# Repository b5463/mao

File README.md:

# MAO firmware

Firmware for **MAO**, the ODD JOBS handheld controller. Current stage: **M2** (in progress)
(ODD BUS v1 over ESP-NOW: discovery and generic capability control).

- Boards (one tree, chosen by target, see below):
  - Espressif **ESP32-C3-LCDkit** (ESP32-C3 rev v0.4, 4 MB flash, no PSRAM): the M0-M2 platform
  - **MAO_MAIN A0** (ESP32-S3-WROOM-1-N8R2: 8 MB flash, 2 MB PSRAM): the custom PCB,
    see [docs/firmware/mao-a0-firmware.md](docs/firmware/mao-a0-firmware.md)
- Framework: native ESP-IDF **v6.0.3**
- UI: LVGL 9.4 via `esp_lvgl_port`, GC9A01 240×240 round display

## Build and flash

The project uses a private ESP-IDF install at `%USERPROFILE%\esp\v6.0.3\esp-idf`
(tools in `%USERPROFILE%\.espressif`). `tools/idf.ps1` activates it for one
PowerShell process and forwards arguments to `idf.py`. Run it from
PowerShell, not Git Bash; ESP-IDF refuses to run under MSYS.

```powershell
.\tools\idf.ps1 build
.\tools\idf.ps1 -p COM13 flash monitor     # check the port first: VID:PID 303A:1001
```

Override the IDF location with `MAO_IDF_PATH` if needed.

The target selects the board (Kconfig "MAO board" follows it):

| Target | Board | Target defaults | Partition table |
|---|---|---|---|
| `esp32c3` | ESP32-C3-LCDkit | `sdkconfig.defaults.esp32c3` | `partitions.csv` (4 MB) |
| `esp32s3` | MAO_MAIN A0 | `sdkconfig.defaults.esp32s3` | `partitions_8mb.csv` (8 MB) |

`set-target` switches a build directory to another board. It deletes that
directory's generated `sdkconfig`, and each profile has its own, so run it once
per profile:

```powershell
.\tools\idf.ps1 set-target esp32s3            # dev profile -> MAO_MAIN A0
.\tools\idf.ps1 release set-target esp32s3    # release profile too
.\tools\idf.ps1 set-target esp32c3            # back to the LCDkit
```

IDF applies `sdkconfig.defaults`, then `sdkconfig.defaults.<target>`, then
the profile file. Component versions are pinned per target in
`dependencies.lock.<target>`. Without the wrapper (Linux, CI, Docker):

```sh
idf.py -B build-s3 -D SDKCONFIG=build-s3/sdkconfig \
       -D SDKCONFIG_DEFAULTS="sdkconfig.defaults;sdkconfig.dev" set-target esp32s3 build
```

Build profiles layer over `sdkconfig.defaults`:

| Profile | Command | Output | Differences |
|---|---|---|---|
| dev (default) | `.\tools\idf.ps1 build` | `build/` | dev console, perf probe, INFO logs |
| release | `.\tools\idf.ps1 release build` | `build-release/` | no console/probe, WARN logs |
| factory | `.\tools\idf.ps1 factory build` | `build-factory/` | dev + the board self-test at every boot (assembled-board validation only, never ship) |

## Layout

Data flow: drivers (input, power, IR) → event bus → `mao_app` (state) → `mao_ui` / `mao_character` / `mao_audio` / `mao_haptics` / `mao_led`.
Sensor observations (`mao_sense`) go to `mao_perception`, which posts interpreted percepts (APPROACH_NEAR, PICKED_UP,
GENTLE_PET, ...) on the event bus; the character never reads hardware and no sensor maps straight to an animation.

| Path | Purpose |
|---|---|
| `main/` | `app_main()`: bring-up sequencing only |
| `components/mao_board` | The only code that knows GPIOs, I2C addresses and board wiring. One implementation per board under `boards/` (`lcdkit/`, `main_a0/`), picked by Kconfig; pin headers are private (the A0 one is generated from `hardware/mao/design/pinmap.py`) |
| `components/mao_display` | GC9A01 + LVGL runtime, display lock, backlight, frame-performance probe |
| `components/mao_input` | Quadrature decoder (EC11 on the LCDkit, Hall ring on the A0; 30 detents/rev) and push-switch state machine, which emit MAO events |
| `components/mao_audio` | Non-blocking synthesised UI sounds: tick, notice, confirm, back |
| `components/mao_led` | WS2812 status LED: off at rest, brief pulses (A0: not fitted, calls are no-ops) |
| `components/mao_ir` | NEC IR TX/RX on the A0 (RMT); disabled on the LCDkit until its jumper is verified |
| `components/mao_haptics` | DRV2605L LRA driver and the haptic vocabulary (A0) |
| `components/mao_power` | Fuel gauge, charger/USB events, power states and sleep, deep-sleep continuity (A0) |
| `components/mao_sense` | IMU, ToF (ST VL53L4CD ULD vendored), light, touch and mic-level observations (A0) |
| `components/mao_perception` | Perception: observations + input → percepts (filters, hysteresis, fusion, confidence); platform-independent engine in `core/` |
| `components/mao_selftest` | Boot check (hardware faults, first boot of a board) and the factory / board self-test |
| `components/mao_system` | Boot banner, event bus + dispatcher, idle timer, settings (NVS `mao`), dev console |
| `components/mao_app` | Application behaviour and the authoritative app state (`mao_state.c`); reactions to percepts (`mao_app_percept.c`); power policy feed (`mao_app_power.c`) |
| `components/mao_ui` | Views: HOME, menu shell, placeholder pages, first encounter; transitions |
| `components/mao_character` | Procedural character: reaction states, idle behaviour, spring motion |
| `components/mao_radio` | Wi-Fi STA (never associated) + ESP-NOW transport |
| `components/odd_bus` | ODD BUS v1: shared, product-agnostic protocol (also used by device firmware) |
| `components/mao_devices` | ODD BUS controller: registry, discovery, liveness, confirmed value control |
| `devices/lamp_01_test` | LAMP 01: minimal ODD BUS test light (POWER, LEVEL) for a second ESP32-C3 |
| `tests/host` | Host unit tests of the perception engine and the power policy (`tests/host/run.sh`) |
| `assets/`, `tools/` | Assets (unused so far), helper scripts (incl. `factory_test.py`) |

## Development tools

With `CONFIG_MAO_DEV_CONSOLE=y` (default) the firmware accepts line commands
on the USB console. Release builds should disable it, along with
`CONFIG_MAO_PERF_PROBE`.

```powershell
python tools\mao_cmd.py COM13 help
python tools\mao_cmd.py COM13 status              # view, dial, encoder counters, heap
python tools\mao_cmd.py COM13 reset-first-boot    # clears only MAO's first-boot key
python tools\mao_cmd.py COM13 reboot
python tools\mao_cmd.py COM13 stress 20 --listen 25
python tools\mao_smoke.py COM13 --cycles 5        # scripted walk through every view and gesture
python tools\mao_cmd.py COM13 odd-selftest        # ODD BUS codec self-test on target
python tools\mao_cmd.py COM13 odd-flood 30        # 50 Hz radio load (coexistence testing)
python tools\mao_cmd.py COM13 board               # caps, revision, I2C scan, rails
python tools\mao_cmd.py COM13 sense               # A0: latest observation of every sensor
python tools\mao_cmd.py COM13 haptic heartbeat    # A0: tick double_tap heartbeat short_pulse tremor annoyed_buzz wake_pulse confirm
python tools\mao_cmd.py COM13 ir send 0x10 0x2A   # A0: one NEC frame
python tools\mao_cmd.py COM13 power               # A0: battery, charger, power state, sleep continuity
python tools\mao_cmd.py COM13 sleep 60            # A0: deep sleep, timer wake after 60 s (also: sleep light 30)
python tools\mao_cmd.py COM13 percept             # perception status; "percept inject GENTLE_PET" tries a reaction
python tools\mao_cmd.py COM13 rotate 270          # display rotation live (bring-up); "rotate save" keeps it
python tools\factory_test.py COM13                # board self-test with operator prompts (docs/hardware/mao-factory-test.md)
sh tests/host/run.sh                              # host unit tests (perception engine, power policy)
python tools\odd_m2_test.py --mao COM13 --lamp COMx   # end-to-end with LAMP 01
```

ESP-NOW runs on the fixed development channel `ODD_BUS_DEV_CHANNEL` (1) with
unencrypted peers: **development network only**.

## Partition map (4 MB, LCDkit)

| Name | Offset | Size |
|---|---|---|
| bootloader | 0x000000 | 32 KB |
| partition table | 0x008000 | 4 KB |
| nvs | 0x009000 | 24 KB |
| otadata | 0x00F000 | 8 KB |
| phy_init | 0x011000 | 4 KB |
| coredump | 0x012000 | 56 KB |
| ota_0 | 0x020000 | 1792 KB |
| ota_1 | 0x1E0000 | 1792 KB |
| assets | 0x3A0000 | 384 KB |

## Partition map (8 MB, MAO_MAIN A0)

The first 128 KB are identical to the 4 MB table.

| Name | Offset | Size |
|---|---|---|
| nvs / otadata / phy_init / coredump | 0x009000 … 0x01FFFF | as above |
| ota_0 | 0x020000 | 3072 KB |
| ota_1 | 0x320000 | 3072 KB |
| assets | 0x620000 | 1536 KB |
| (unallocated reserve) | 0x7A0000 | 384 KB |

## Recovery

A verified dump of the original factory firmware lives in `../backup/`
(SHA-256 `a15e09ff…41c10`). To restore it:

```powershell
python -m esptool --port COM13 write-flash 0x0 ..\backup\mao_flash_full_20260923.bin
```

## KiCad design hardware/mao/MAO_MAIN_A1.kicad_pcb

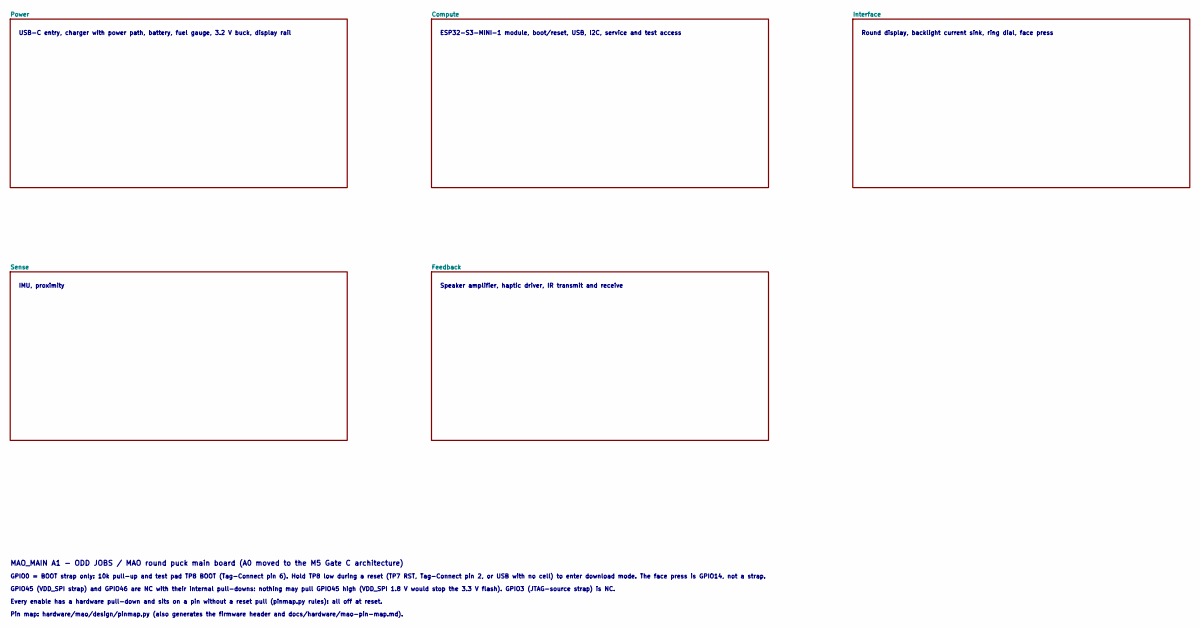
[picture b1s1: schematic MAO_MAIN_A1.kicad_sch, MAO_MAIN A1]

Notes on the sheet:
USB-C entry, charger with power path, battery, fuel gauge, 3.2 V buck, display rail
ESP32-S3-MINI-1 module, boot/reset, USB, I2C, service and test access
Round display, backlight current sink, ring dial, face press
IMU, proximity
Speaker amplifier, haptic driver, IR transmit and receive
MAO_MAIN A1 - ODD JOBS / MAO round puck main board (A0 moved to the M5 Gate C architecture)
GPIO0 = BOOT strap only: 10k pull-up and test pad TP8 BOOT (Tag-Connect pin 6). Hold TP8 low during a reset (TP7 RST, Tag-Connect pin 2, or USB with no cell) to enter download mode. The face press is GPIO14, not a strap.
GPIO45 (VDD_SPI strap) and GPIO46 are NC with their internal pull-downs: nothing may pull GPIO45 high (VDD_SPI 1.8 V would stop the 3.3 V flash). GPIO3 (JTAG-source strap) is NC.
Every enable has a hardware pull-down and sits on a pin without a reset pull (pinmap.py rules): all off at reset.
Pin map: hardware/mao/design/pinmap.py (also generates the firmware header and docs/hardware/mao-pin-map.md).

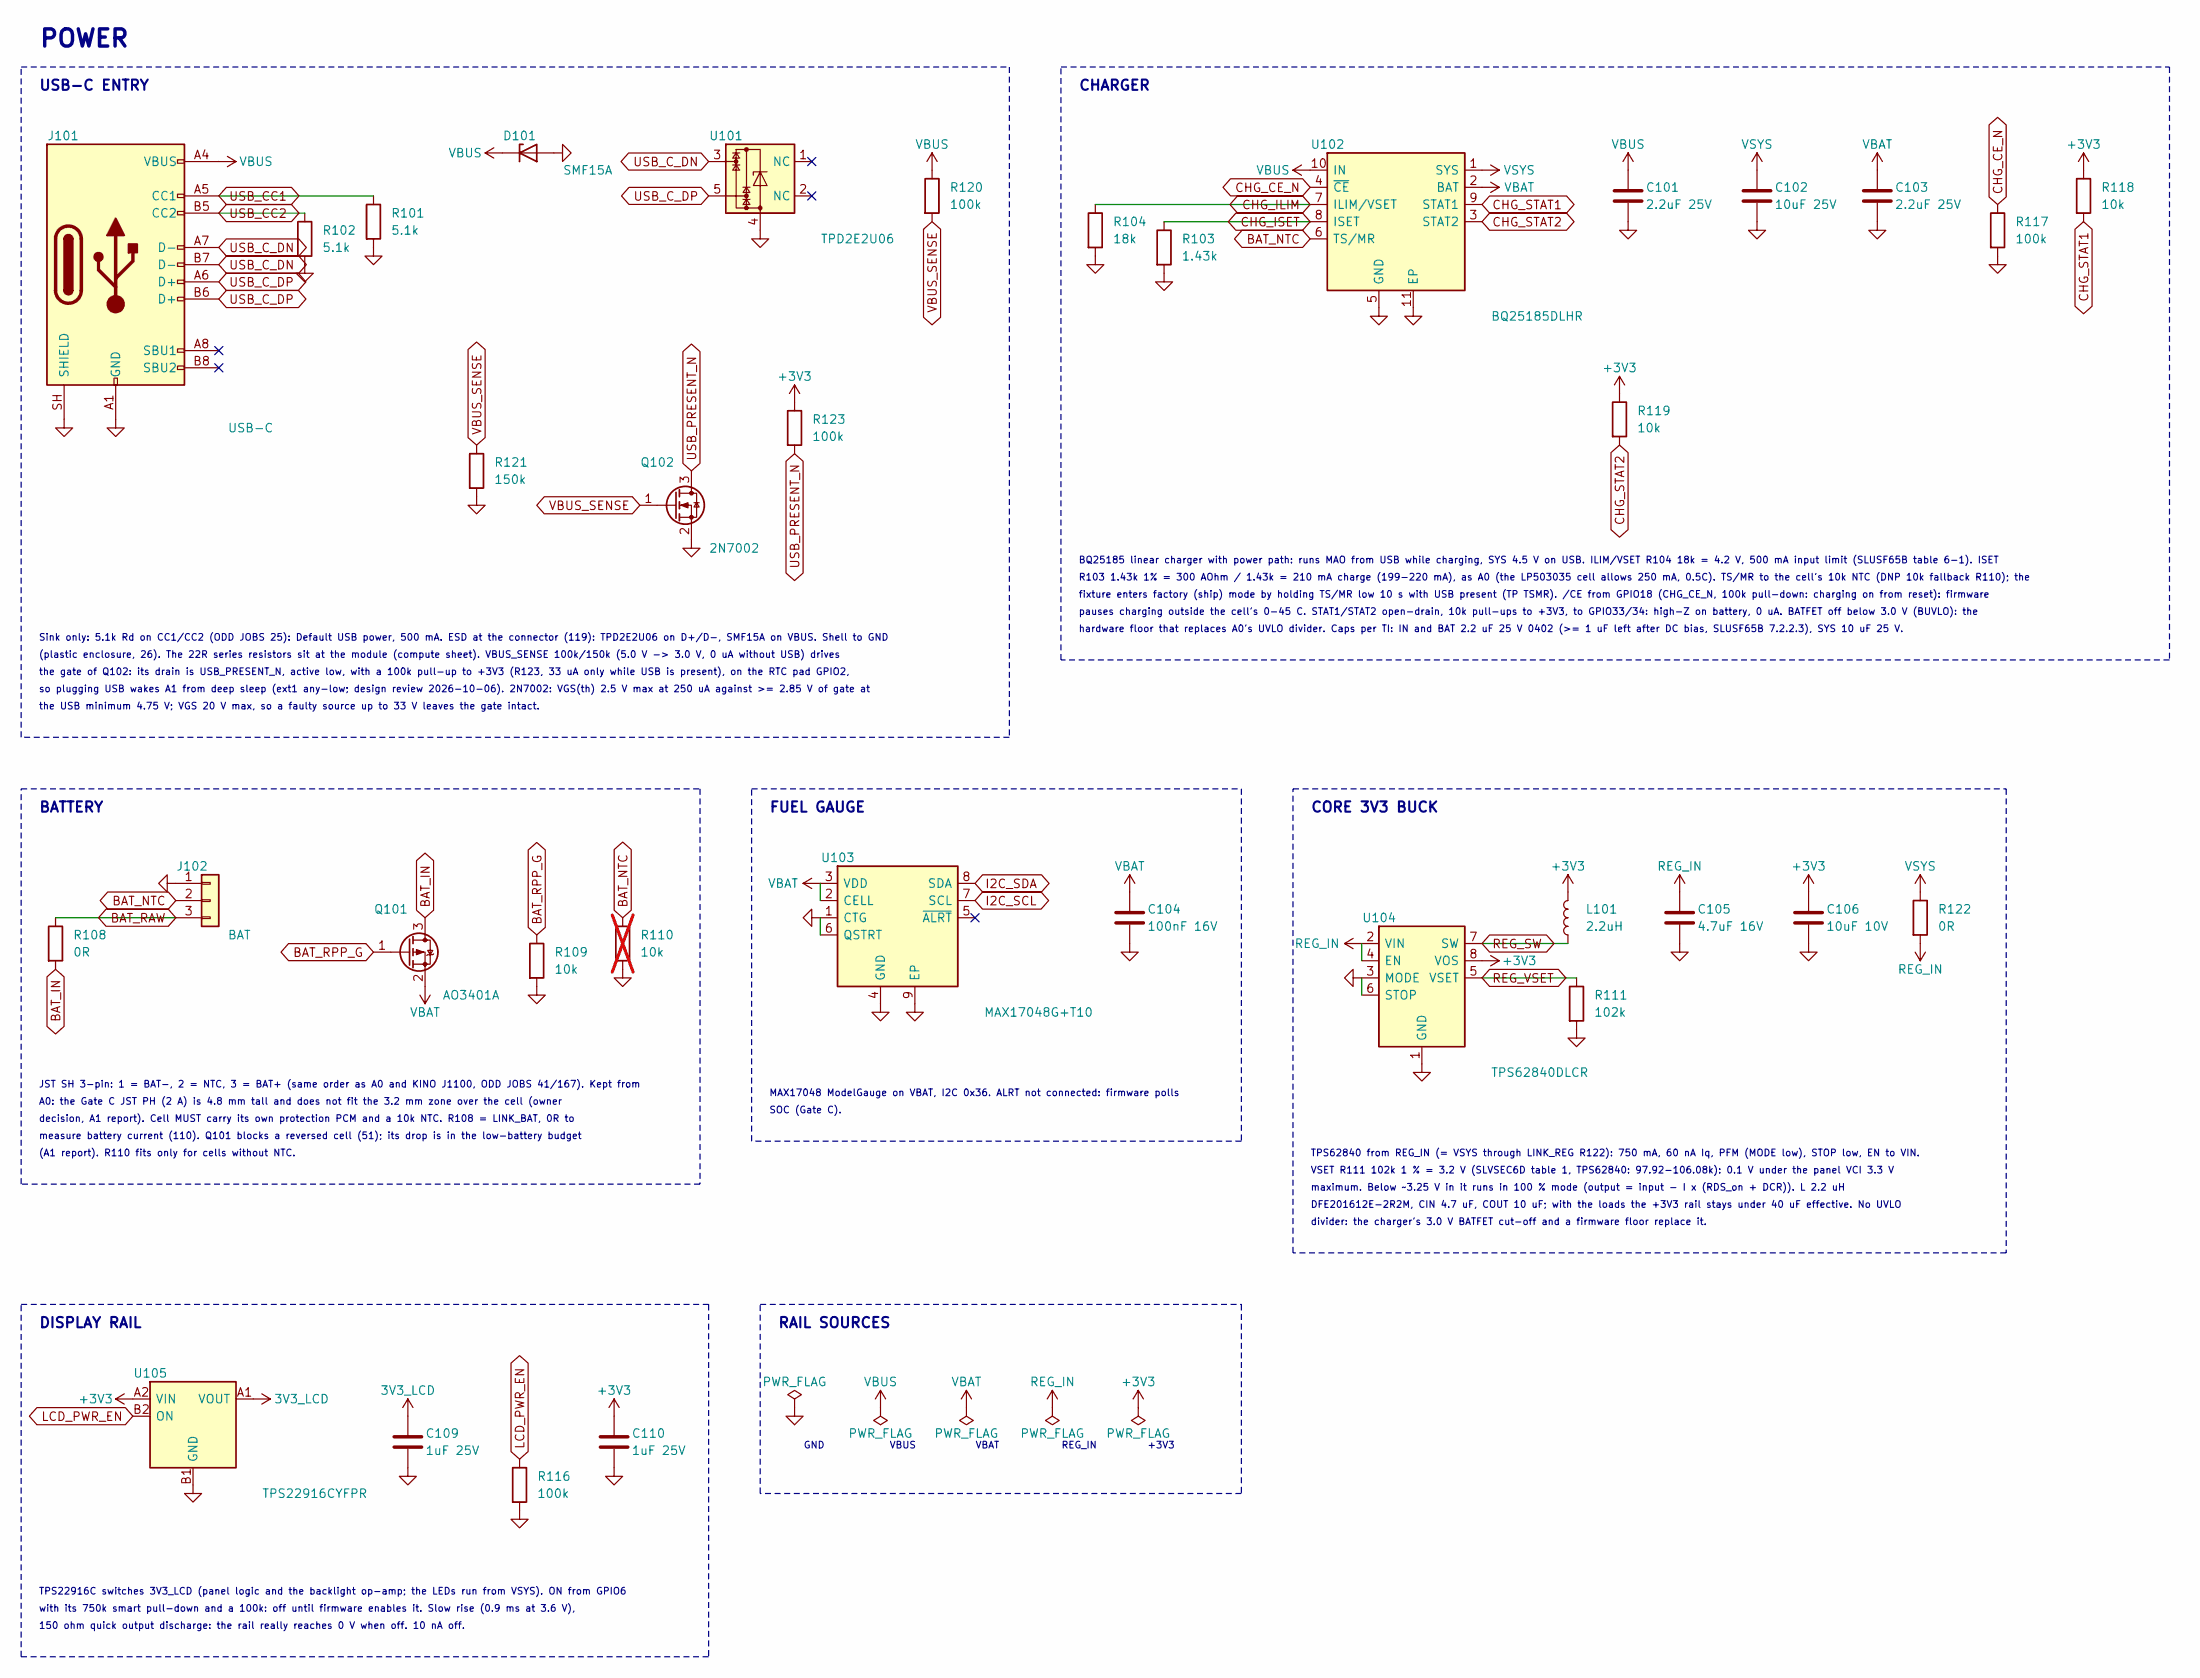
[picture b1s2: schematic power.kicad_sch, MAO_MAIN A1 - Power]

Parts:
C101, C103: 2.2uF 25V; C_0402_1005Metric; MPN CL05A225KA5NUNC; LCSC C307418
C102: 10uF 25V; C_0603_1608Metric; MPN CL10A106MA8NRNC; LCSC C96446
C104: 100nF 16V; C_0402_1005Metric; MPN CL05B104KO5NNNC; LCSC C1525
C105: 4.7uF 16V; C_0603_1608Metric; MPN CL10A475KO8NNNC; LCSC C19666
C106: 10uF 10V; C_0603_1608Metric; MPN CL10A106KP8NNNC; LCSC C19702
C109, C110: 1uF 25V; C_0402_1005Metric; MPN CL05A105KA5NQNC; LCSC C52923
D101: SMF15A; D_SMF; MPN SMF15A; LCSC C123802
J101: USB-C; USB_C_Receptacle_HRO_TYPE-C-31-M-12; MPN TYPE-C-31-M-12; LCSC C165948
J102: BAT; JST_SH_SM03B-SRSS-TB_1x03-1MP_P1.00mm_Horizontal; MPN ZX-SH1.0-3PWT (JST SM03B-SRSS-TB compat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; LCSC C7430445
L101: 2.2uH; L_Murata_DFE201610P; MPN DFE201612E-2R2M=P2; LCSC C337893
Q101: AO3401A; SOT-23; MPN AO3401A; LCSC C15127
Q102: 2N7002; SOT-23; MPN 2N7002; LCSC C8545
R101, R102: 5.1k; R_0402_1005Metric; MPN 0402WGF5101TCE; LCSC C25905
R103: 1.43k; R_0402_1005Metric; MPN RC0402FR-071K43L; LCSC C163483
R104: 18k; R_0402_1005Metric; MPN 0402WGF1802TCE; LCSC C25762
R108: 0R; R_1206_3216Metric; MPN 1206W4F0000T5E; LCSC C17888
R109, R118, R119: 10k; R_0402_1005Metric; MPN 0402WGF1002TCE; LCSC C25744
R110: 10k; R_0402_1005Metric; MPN 0402WGF1002TCE; LCSC C25744; not fitted
R111: 102k; R_0402_1005Metric; MPN FRC0402F1023TS; LCSC C2933066
R116, R117, R120, R123: 100k; R_0402_1005Metric; MPN 0402WGF1003TCE; LCSC C25741
R121: 150k; R_0402_1005Metric; MPN 0402WGF1503TCE; LCSC C25755
R122: 0R; R_0603_1608Metric; MPN 0603WAF0000T5E; LCSC C21189
U101: TPD2E2U06; SOT-553; MPN TPD2E2U06DRLR; LCSC C1972959
U102: BQ25185DLHR; Texas_DLH0010A_WSON-10-1EP_2.2x2mm_P0.4mm_EP0.9x1.5mm; MPN BQ25185DLHR; LCSC C19725033
U103: MAX17048G+T10; TDFN-8-1EP_2x2mm_P0.5mm_EP0.8x1.2mm; MPN MAX17048G+T10; LCSC C2682616
U104: TPS62840DLCR; TI_DLC0008B_VSON-HR-8_1.5x2mm_P0.5mm; MPN TPS62840DLCR; LCSC C2071859
U105: TPS22916CYFPR; Texas_PicoStar_BGA-4_0.758x0.758mm_Layout2x2_P0.4mm; MPN TPS22916CYFPR; LCSC C2680319

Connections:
3V3_LCD: C109.1, U105.A1 (VOUT); also elsewhere on the board
+3V3: C106.1, C110.1, L101.2, R118.1, R119.1, R123.1, U104.8 (VOS), U105.A2 (VIN); also elsewhere on the board
BAT_IN: Q101.3 (D), R108.2
BAT_NTC: J102.2, R110.1, U102.6 (TS/MR); also elsewhere on the board
BAT_RAW: J102.3, R108.1
BAT_RPP_G: Q101.1 (G), R109.1
CHG_CE_N: R117.1, U102.4 (~CE); also elsewhere on the board
CHG_ILIM: R104.1, U102.7 (ILIM/VSET)
CHG_ISET: R103.1, U102.8 (ISET)
CHG_STAT1: R118.2, U102.9 (STAT1); also elsewhere on the board
CHG_STAT2: R119.2, U102.3 (STAT2); also elsewhere on the board
GND: C101.2, C102.2, C103.2, C104.2, C105.2, C106.2, C109.2, C110.2, D101.2 (A), J101.A1 (GND), J101.A12 (GND), J101.B1 (GND), J101.B12 (GND), J101.SH (SHIELD), J102.1, Q102.2 (S), R101.2, R102.2, R103.2, R104.2, R109.2, R110.2, R111.2, R116.2, R117.2, R121.2, U101.4, U102.5 (GND), U102.11 (EP), U103.1 (CTG), U103.4 (GND), U103.6 (QSTRT), U103.9 (EP), U104.1 (GND), U104.3 (MODE), U104.6 (STOP), U105.B1 (GND); also elsewhere on the board
I2C_SCL: U103.7 (SCL); also elsewhere on the board
I2C_SDA: U103.8 (SDA); also elsewhere on the board
LCD_PWR_EN: R116.1, U105.B2 (ON); also elsewhere on the board
REG_IN: C105.1, R122.2, U104.2 (VIN), U104.4 (EN)
REG_SW: L101.1, U104.7 (SW)
REG_VSET: R111.1, U104.5 (VSET)
USB_CC1: J101.A5 (CC1), R101.1
USB_CC2: J101.B5 (CC2), R102.1
USB_C_DN: J101.A7 (D-), J101.B7 (D-), U101.3; also elsewhere on the board
USB_C_DP: J101.A6 (D+), J101.B6 (D+), U101.5; also elsewhere on the board
USB_PRESENT_N: Q102.3 (D), R123.2; also elsewhere on the board
VBAT: C103.1, C104.1, Q101.2 (S), U102.2 (BAT), U103.2 (CELL), U103.3 (VDD); also elsewhere on the board
VBUS: C101.1, D101.1 (K), J101.A4 (VBUS), J101.A9 (VBUS), J101.B4 (VBUS), J101.B9 (VBUS), R120.1, U102.10 (IN); also elsewhere on the board
VBUS_SENSE: Q102.1 (G), R120.2, R121.1
VSYS: C102.1, R122.1, U102.1 (SYS); also elsewhere on the board

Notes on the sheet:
POWER
USB-C ENTRY
Sink only: 5.1k Rd on CC1/CC2 (ODD JOBS 25): Default USB power, 500 mA. ESD at the connector (119): TPD2E2U06 on D+/D-, SMF15A on VBUS. Shell to GND
(plastic enclosure, 26). The 22R series resistors sit at the module (compute sheet). VBUS_SENSE 100k/150k (5.0 V -> 3.0 V, 0 uA without USB) drives
the gate of Q102: its drain is USB_PRESENT_N, active low, with a 100k pull-up to +3V3 (R123, 33 uA only while USB is present), on the RTC pad GPIO2,
so plugging USB wakes A1 from deep sleep (ext1 any-low; design review 2026-10-06). 2N7002: VGS(th) 2.5 V max at 250 uA against >= 2.85 V of gate at
the USB minimum 4.75 V; VGS 20 V max, so a faulty source up to 33 V leaves the gate intact.
CHARGER
BQ25185 linear charger with power path: runs MAO from USB while charging, SYS 4.5 V on USB. ILIM/VSET R104 18k = 4.2 V, 500 mA input limit (SLUSF65B table 6-1). ISET
R103 1.43k 1% = 300 AOhm / 1.43k = 210 mA charge (199-220 mA), as A0 (the LP503035 cell allows 250 mA, 0.5C). TS/MR to the cell's 10k NTC (DNP 10k fallback R110); the
fixture enters factory (ship) mode by holding TS/MR low 10 s with USB present (TP TSMR). /CE from GPIO18 (CHG_CE_N, 100k pull-down: charging on from reset): firmware
pauses charging outside the cell's 0-45 C. STAT1/STAT2 open-drain, 10k pull-ups to +3V3, to GPIO33/34: high-Z on battery, 0 uA. BATFET off below 3.0 V (BUVLO): the
hardware floor that replaces A0's UVLO divider. Caps per TI: IN and BAT 2.2 uF 25 V 0402 (>= 1 uF left after DC bias, SLUSF65B 7.2.2.3), SYS 10 uF 25 V.
BATTERY
JST SH 3-pin: 1 = BAT-, 2 = NTC, 3 = BAT+ (same order as A0 and KINO J1100, ODD JOBS 41/167). Kept from
A0: the Gate C JST PH (2 A) is 4.8 mm tall and does not fit the 3.2 mm zone over the cell (owner
decision, A1 report). Cell MUST carry its own protection PCM and a 10k NTC. R108 = LINK_BAT, 0R to
measure battery current (110). Q101 blocks a reversed cell (51); its drop is in the low-battery budget
(A1 report). R110 fits only for cells without NTC.
FUEL GAUGE
MAX17048 ModelGauge on VBAT, I2C 0x36. ALRT not connected: firmware polls
SOC (Gate C).
CORE 3V3 BUCK
TPS62840 from REG_IN (= VSYS through LINK_REG R122): 750 mA, 60 nA Iq, PFM (MODE low), STOP low, EN to VIN.
VSET R111 102k 1 % = 3.2 V (SLVSEC6D table 1, TPS62840: 97.92-106.08k): 0.1 V under the panel VCI 3.3 V
maximum. Below ~3.25 V in it runs in 100 % mode (output = input - I x (RDS_on + DCR)). L 2.2 uH
DFE201612E-2R2M, CIN 4.7 uF, COUT 10 uF; with the loads the +3V3 rail stays under 40 uF effective. No UVLO
divider: the charger's 3.0 V BATFET cut-off and a firmware floor replace it.
DISPLAY RAIL
TPS22916C switches 3V3_LCD (panel logic and the backlight op-amp; the LEDs run from VSYS). ON from GPIO6
with its 750k smart pull-down and a 100k: off until firmware enables it. Slow rise (0.9 ms at 3.6 V),
150 ohm quick output discharge: the rail really reaches 0 V when off. 10 nA off.
RAIL SOURCES
GND
VBUS
VBAT
REG_IN
+3V3

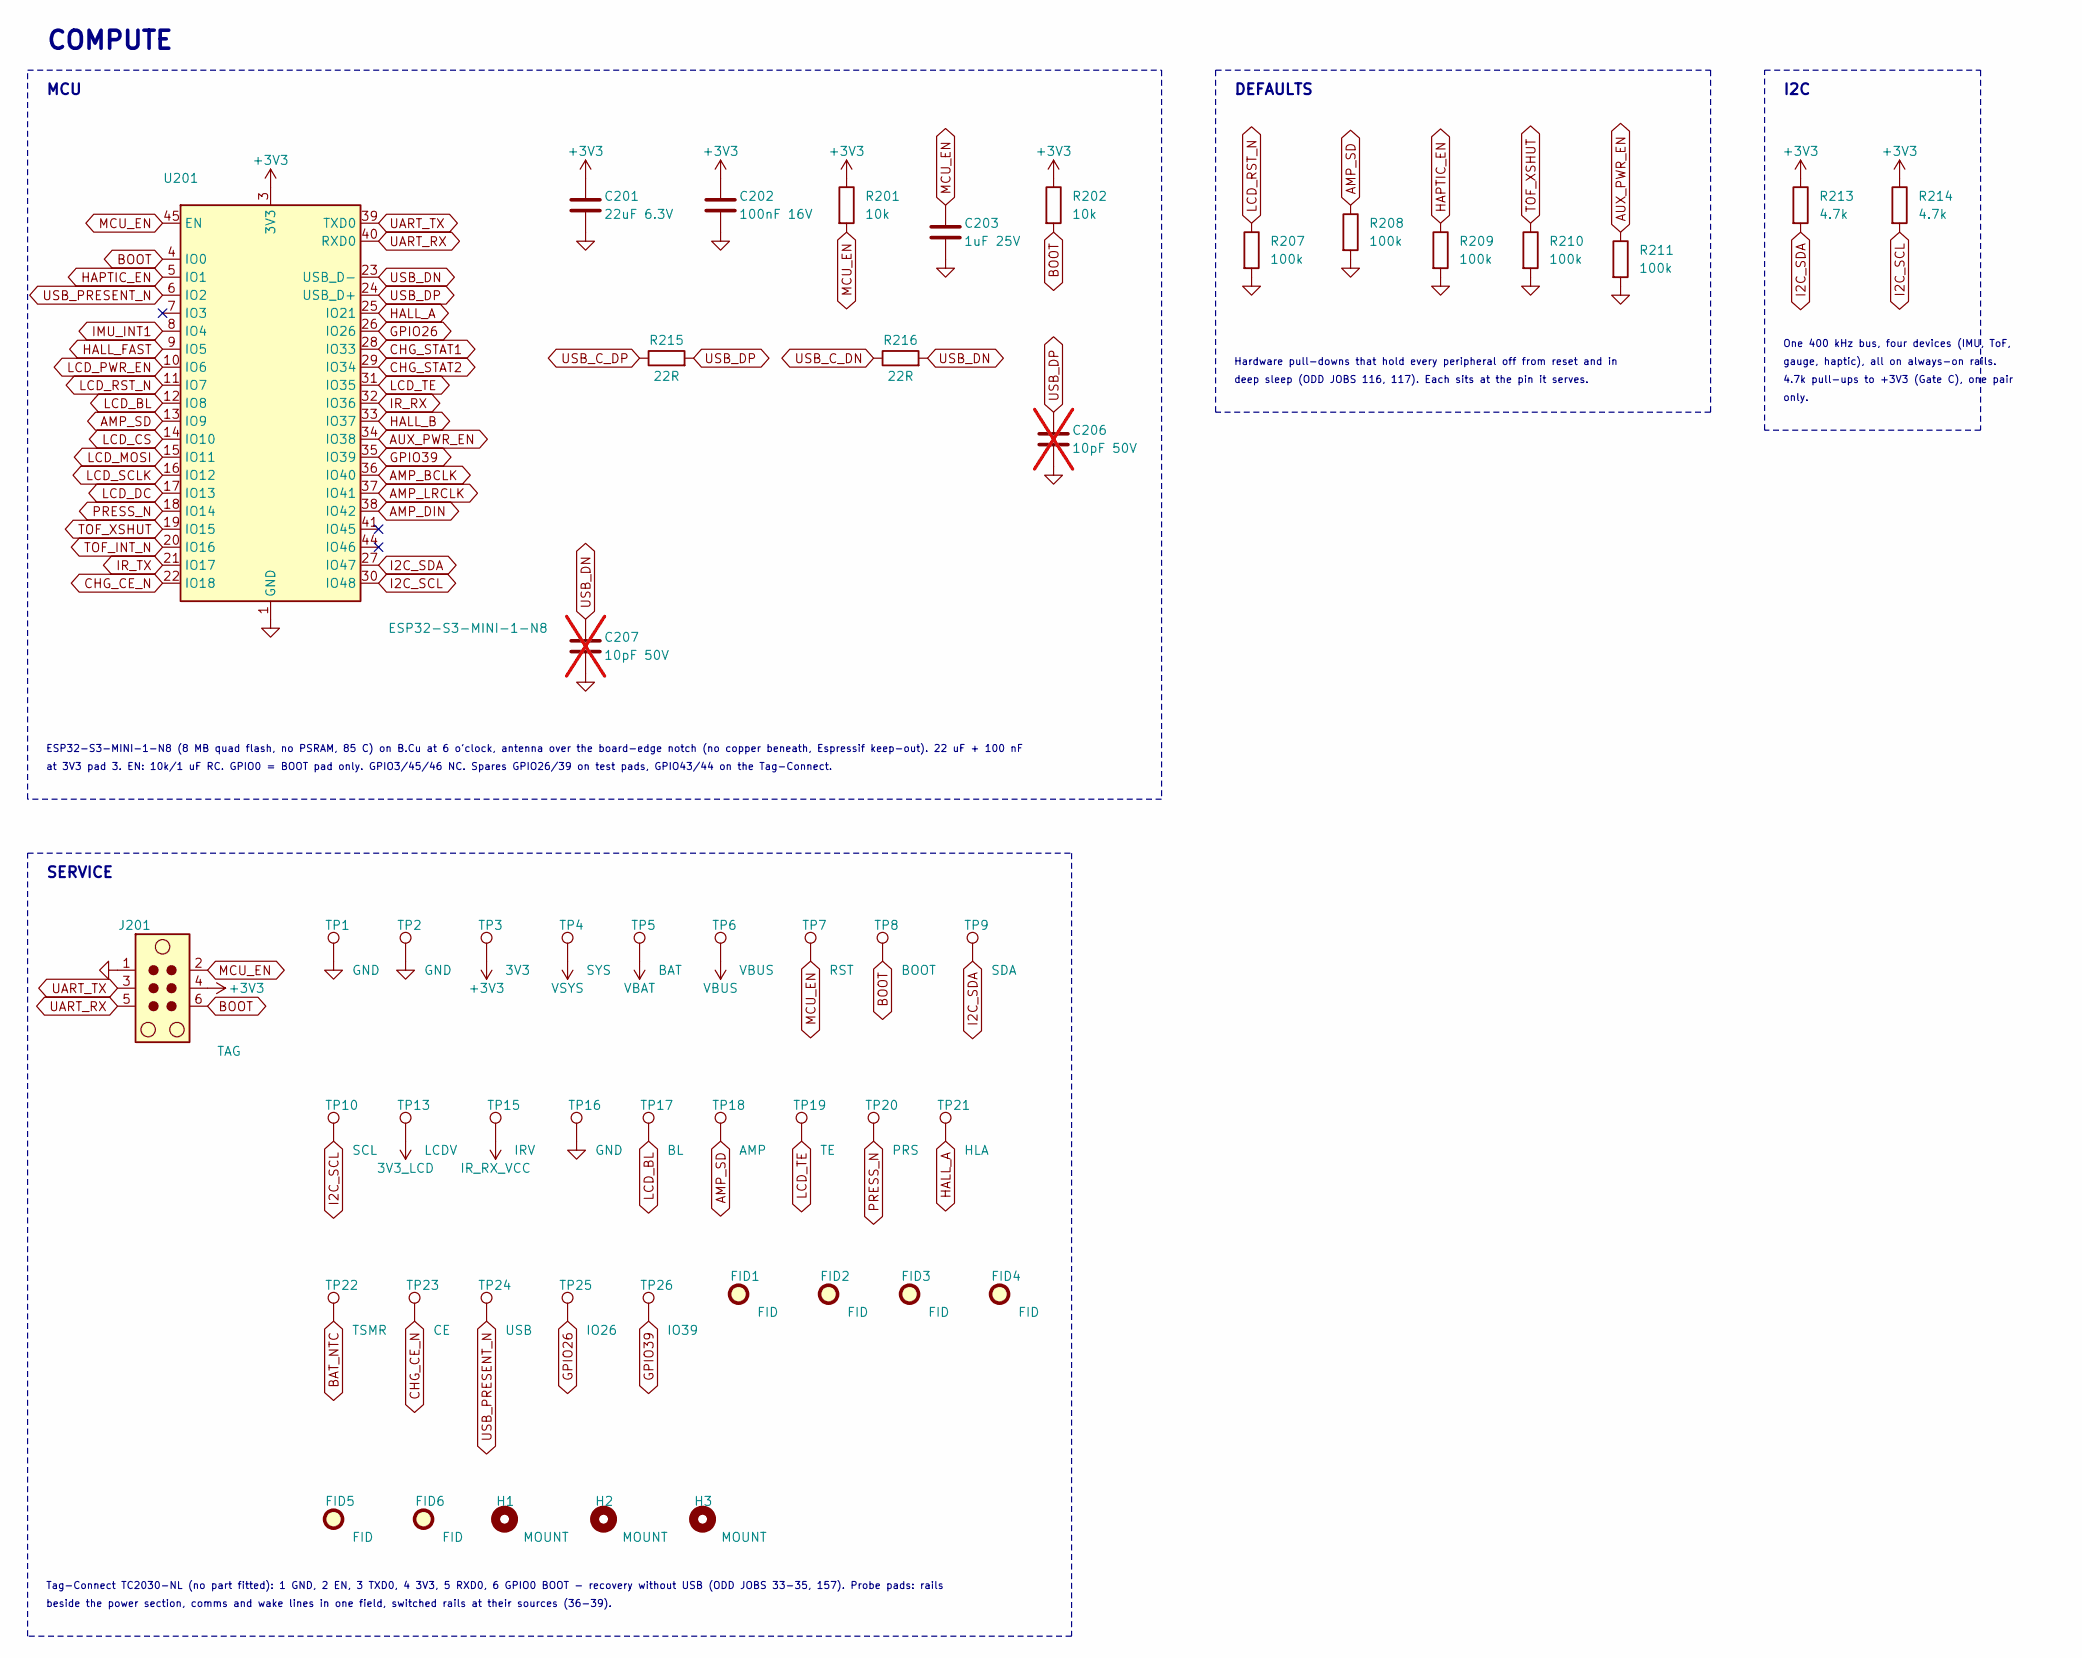
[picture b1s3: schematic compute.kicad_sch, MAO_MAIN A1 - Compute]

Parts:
C201: 22uF 6.3V; C_0603_1608Metric; MPN CL10A226MQ8NRNC; LCSC C59461
C202: 100nF 16V; C_0402_1005Metric; MPN CL05B104KO5NNNC; LCSC C1525
C203: 1uF 25V; C_0402_1005Metric; MPN CL05A105KA5NQNC; LCSC C52923
C206, C207: 10pF 50V; C_0402_1005Metric; MPN CL05C100CB5NNNC; LCSC C318588; not fitted
FID1, FID2, FID3, FID4, FID5, FID6: FID; Fiducial_1mm_Mask2mm; MPN PCB feature, no part
H1, H2: MOUNT; MountingHole_2.2mm_M2; MPN PCB feature, no part
H3: MOUNT; MountingHole_2mm; MPN PCB feature, no part
J201: TAG; Tag-Connect_TC2030-IDC-NL_2x03_P1.27mm_Vertical; MPN PCB feature, no part
R201, R202: 10k; R_0402_1005Metric; MPN 0402WGF1002TCE; LCSC C25744
R207, R208, R209, R210, R211: 100k; R_0402_1005Metric; MPN 0402WGF1003TCE; LCSC C25741
R213, R214: 4.7k; R_0402_1005Metric; MPN 0402WGF4701TCE; LCSC C25900
R215, R216: 22R; R_0402_1005Metric; MPN 0402WGF220JTCE; LCSC C25092
TP1, TP2, TP16: GND; TestPoint_Pad_D1.2mm; MPN PCB feature, no part
TP3: 3V3; TestPoint_Pad_D1.2mm; MPN PCB feature, no part
TP4: SYS; TestPoint_Pad_D1.2mm; MPN PCB feature, no part
TP5: BAT; TestPoint_Pad_D1.2mm; MPN PCB feature, no part
TP6: VBUS; TestPoint_Pad_D1.2mm; MPN PCB feature, no part
TP7: RST; TestPoint_Pad_D1.0mm; MPN PCB feature, no part
TP8: BOOT; TestPoint_Pad_D1.0mm; MPN PCB feature, no part
TP9: SDA; TestPoint_Pad_D1.0mm; MPN PCB feature, no part
TP10: SCL; TestPoint_Pad_D1.0mm; MPN PCB feature, no part
TP13: LCDV; TestPoint_Pad_D1.0mm; MPN PCB feature, no part
TP15: IRV; TestPoint_Pad_D1.0mm; MPN PCB feature, no part
TP17: BL; TestPoint_Pad_D1.0mm; MPN PCB feature, no part
TP18: AMP; TestPoint_Pad_D1.0mm; MPN PCB feature, no part
TP19: TE; TestPoint_Pad_D1.0mm; MPN PCB feature, no part
TP20: PRS; TestPoint_Pad_D1.0mm; MPN PCB feature, no part
TP21: HLA; TestPoint_Pad_D1.0mm; MPN PCB feature, no part
TP22: TSMR; TestPoint_Pad_D1.0mm; MPN PCB feature, no part
TP23: CE; TestPoint_Pad_D1.0mm; MPN PCB feature, no part
TP24: USB; TestPoint_Pad_D1.0mm; MPN PCB feature, no part
TP25: IO26; TestPoint_Pad_D1.0mm; MPN PCB feature, no part
TP26: IO39; TestPoint_Pad_D1.0mm; MPN PCB feature, no part
U201: ESP32-S3-MINI-1-N8; ESP32-S2-MINI-1; MPN ESP32-S3-MINI-1-N8; LCSC C2913206

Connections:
3V3_LCD: TP13.1; also elsewhere on the board
+3V3: C201.1, C202.1, J201.4, R201.1, R202.1, R213.1, R214.1, TP3.1, U201.3 (3V3); also elsewhere on the board
AMP_BCLK: U201.36 (IO40); also elsewhere on the board
AMP_DIN: U201.38 (IO42); also elsewhere on the board
AMP_LRCLK: U201.37 (IO41); also elsewhere on the board
AMP_SD: R208.1, TP18.1, U201.13 (IO9); also elsewhere on the board
AUX_PWR_EN: R211.1, U201.34 (IO38); also elsewhere on the board
BAT_NTC: TP22.1; also elsewhere on the board
BOOT: J201.6, R202.2, TP8.1, U201.4 (IO0)
CHG_CE_N: TP23.1, U201.22 (IO18); also elsewhere on the board
CHG_STAT1: U201.28 (IO33); also elsewhere on the board
CHG_STAT2: U201.29 (IO34); also elsewhere on the board
GND: C201.2, C202.2, C203.2, C206.2, C207.2, J201.1, R207.2, R208.2, R209.2, R210.2, R211.2, TP1.1, TP2.1, TP16.1, U201.1 (GND), U201.2 (GND), U201.42 (GND), U201.43 (GND), U201.46 (GND), U201.47 (GND), U201.48 (GND), U201.49 (GND), U201.50 (GND), U201.51 (GND), U201.52 (GND), U201.53 (GND), U201.54 (GND), U201.55 (GND), U201.56 (GND), U201.57 (GND), U201.58 (GND), U201.59 (GND), U201.60 (GND), U201.61 (GND), U201.62 (GND), U201.63 (GND), U201.64 (GND), U201.65 (GND); also elsewhere on the board
GPIO26: TP25.1, U201.26 (IO26)
GPIO39: TP26.1, U201.35 (IO39)
HALL_A: TP21.1, U201.25 (IO21); also elsewhere on the board
HALL_B: U201.33 (IO37); also elsewhere on the board
HALL_FAST: U201.9 (IO5); also elsewhere on the board
HAPTIC_EN: R209.1, U201.5 (IO1); also elsewhere on the board
I2C_SCL: R214.2, TP10.1, U201.30 (IO48); also elsewhere on the board
I2C_SDA: R213.2, TP9.1, U201.27 (IO47); also elsewhere on the board
IMU_INT1: U201.8 (IO4); also elsewhere on the board
IR_RX: U201.32 (IO36); also elsewhere on the board
IR_RX_VCC: TP15.1; also elsewhere on the board
IR_TX: U201.21 (IO17); also elsewhere on the board
LCD_BL: TP17.1, U201.12 (IO8); also elsewhere on the board
LCD_CS: U201.14 (IO10); also elsewhere on the board
LCD_DC: U201.17 (IO13); also elsewhere on the board
LCD_MOSI: U201.15 (IO11); also elsewhere on the board
LCD_PWR_EN: U201.10 (IO6); also elsewhere on the board
LCD_RST_N: R207.1, U201.11 (IO7); also elsewhere on the board
LCD_SCLK: U201.16 (IO12); also elsewhere on the board
LCD_TE: TP19.1, U201.31 (IO35); also elsewhere on the board
MCU_EN: C203.1, J201.2, R201.2, TP7.1, U201.45 (EN)
PRESS_N: TP20.1, U201.18 (IO14); also elsewhere on the board
TOF_INT_N: U201.20 (IO16); also elsewhere on the board
TOF_XSHUT: R210.1, U201.19 (IO15); also elsewhere on the board
UART_RX: J201.5, U201.40 (RXD0)
UART_TX: J201.3, U201.39 (TXD0)
USB_C_DN: R216.1; also elsewhere on the board
USB_C_DP: R215.1; also elsewhere on the board
USB_DN: C207.1, R216.2, U201.23 (USB_D-)
USB_DP: C206.1, R215.2, U201.24 (USB_D+)
USB_PRESENT_N: TP24.1, U201.6 (IO2); also elsewhere on the board
VBAT: TP5.1; also elsewhere on the board
VBUS: TP6.1; also elsewhere on the board
VSYS: TP4.1; also elsewhere on the board

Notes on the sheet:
COMPUTE
MCU
ESP32-S3-MINI-1-N8 (8 MB quad flash, no PSRAM, 85 C) on B.Cu at 6 o'clock, antenna over the board-edge notch (no copper beneath, Espressif keep-out). 22 uF + 100 nF
at 3V3 pad 3. EN: 10k/1 uF RC. GPIO0 = BOOT pad only. GPIO3/45/46 NC. Spares GPIO26/39 on test pads, GPIO43/44 on the Tag-Connect.
DEFAULTS
Hardware pull-downs that hold every peripheral off from reset and in
deep sleep (ODD JOBS 116, 117). Each sits at the pin it serves.
I2C
One 400 kHz bus, four devices (IMU, ToF,
gauge, haptic), all on always-on rails.
4.7k pull-ups to +3V3 (Gate C), one pair
only.
SERVICE
Tag-Connect TC2030-NL (no part fitted): 1 GND, 2 EN, 3 TXD0, 4 3V3, 5 RXD0, 6 GPIO0 BOOT - recovery without USB (ODD JOBS 33-35, 157). Probe pads: rails
beside the power section, comms and wake lines in one field, switched rails at their sources (36-39).
